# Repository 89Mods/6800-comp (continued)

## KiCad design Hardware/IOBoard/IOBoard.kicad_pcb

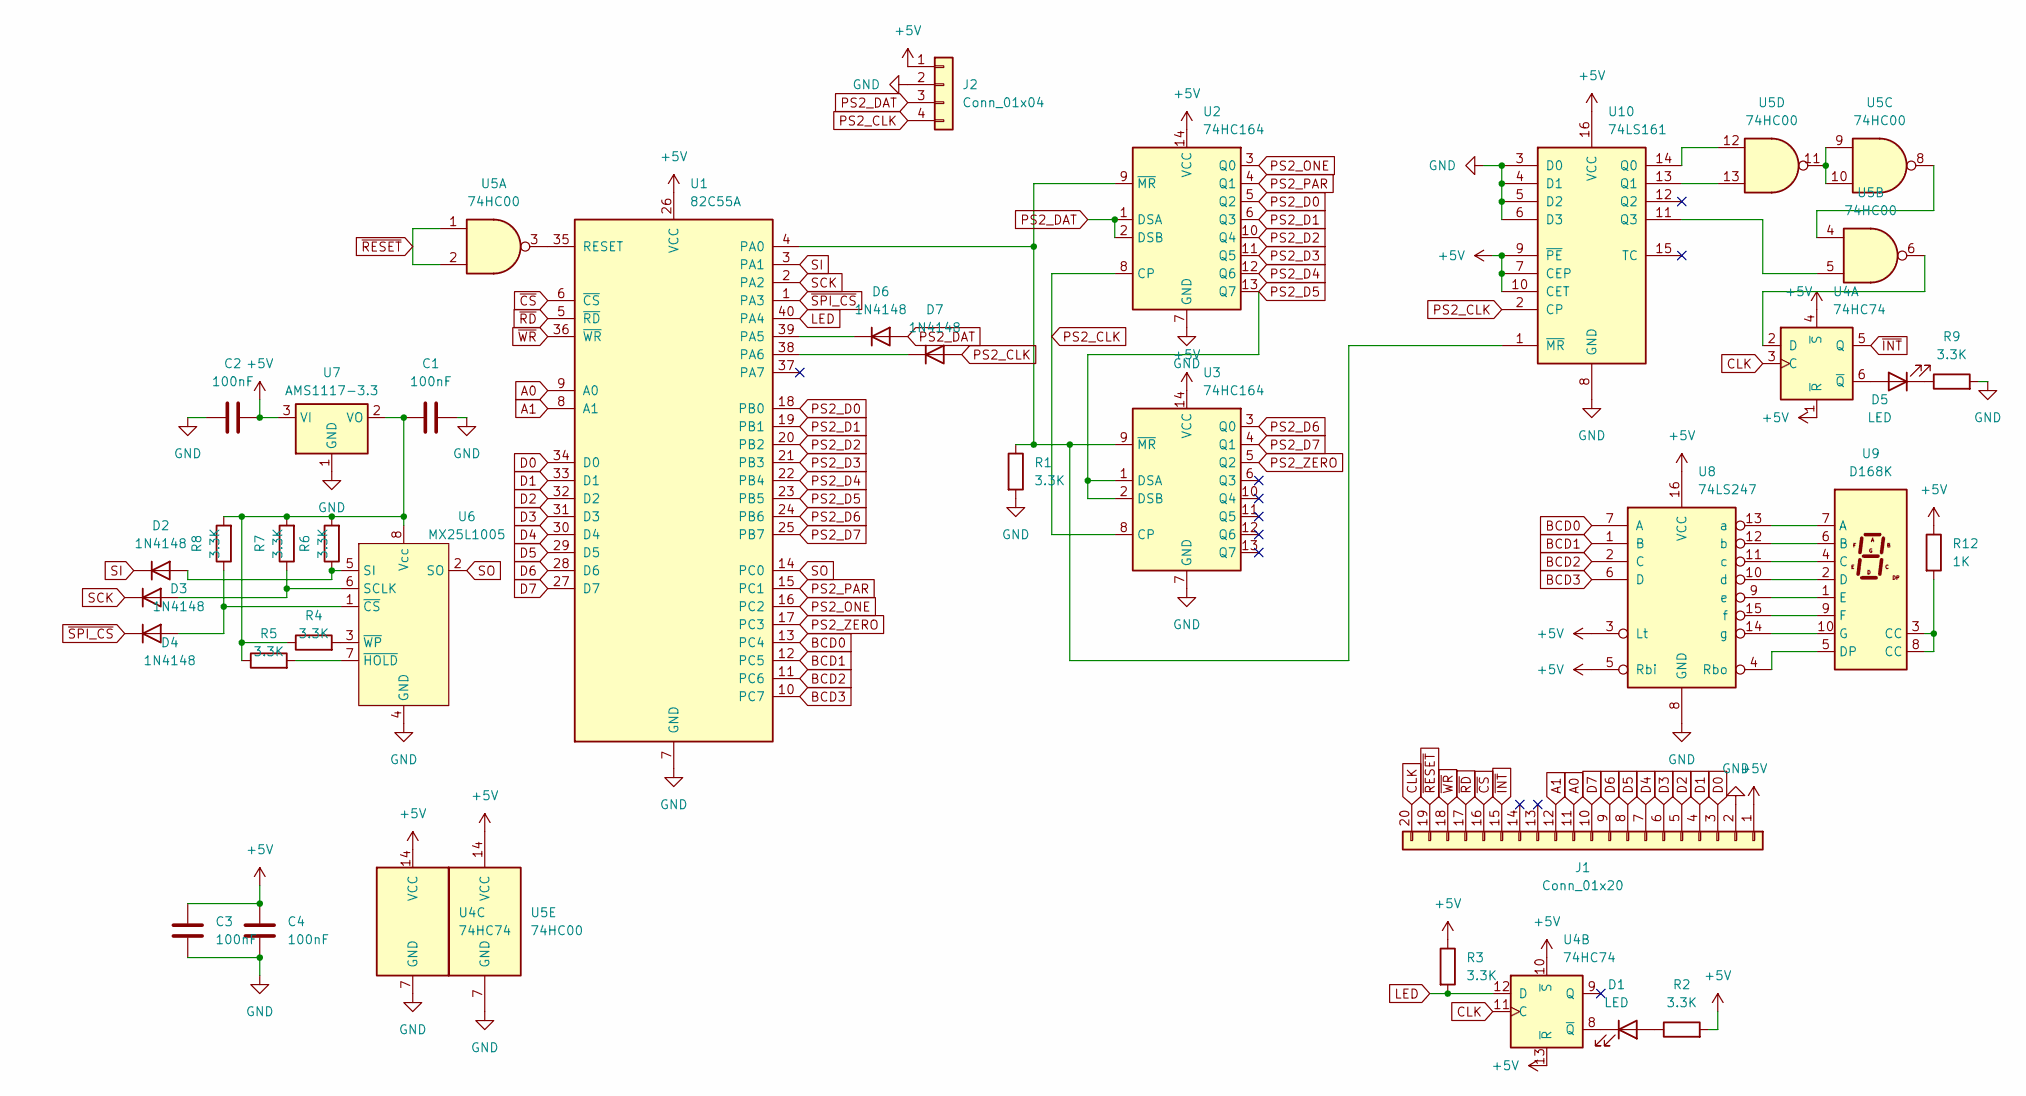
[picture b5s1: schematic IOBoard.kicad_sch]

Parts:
C1, C2, C3, C4: 100nF; C_Disc_D3.0mm_W1.6mm_P2.50mm
D1, D5: LED; LED_D3.0mm
D2, D3, D4, D6, D7: 1N4148; D_DO-34_SOD68_P7.62mm_Horizontal
J1: Conn_01x20; PinHeader_1x20_P2.54mm_Vertical
J2: Conn_01x04; PinHeader_1x04_P2.54mm_Vertical
R1, R2, R3, R4, R5, R6, R7, R8, R9: 3.3K; R_Axial_DIN0204_L3.6mm_D1.6mm_P7.62mm_Horizontal
R12: 1K; R_Axial_DIN0204_L3.6mm_D1.6mm_P7.62mm_Horizontal
U1: 82C55A; DIP-40_W15.24mm
U2, U3: 74HC164; DIP-14_W7.62mm
U4: 74HC74; DIP-14_W7.62mm
U5: 74HC00; DIP-14_W7.62mm
U6: MX25L1005; DIP-8_W7.62mm
U7: AMS1117-3.3; SOT-223-3_TabPin2
U8: 74LS247; DIP-16_W7.62mm
U9: D168K; D1X8K
U10: 74LS161; DIP-16_W7.62mm

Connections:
+5V: C2.2, C3.2, C4.2, J1.1, J2.1, R2.2, R3.1, R12.1, U1.26 (VCC), U2.14 (VCC), U3.14 (VCC), U4.1 (~R), U4.4 (~S), U4.10 (~S), U4.13 (~R), U4.14 (VCC), U5.14 (VCC), U7.3 (VI), U8.3 (Lt), U8.5 (Rbi), U8.16 (VCC), U10.7 (CEP), U10.9 (~PE), U10.10 (CET), U10.16 (VCC)
A0: J1.11, U1.9 (A0)
A1: J1.12, U1.8 (A1)
BCD0: U1.13 (PC4), U8.7 (A)
BCD1: U1.12 (PC5), U8.1 (B)
BCD2: U1.11 (PC6), U8.2 (C)
BCD3: U1.10 (PC7), U8.6 (D)
CLK: J1.20, U4.3 (C), U4.11 (C)
D0: J1.3, U1.34 (D0)
D1: J1.4, U1.33 (D1)
D2: J1.5, U1.32 (D2)
D3: J1.6, U1.31 (D3)
D4: J1.7, U1.30 (D4)
D5: J1.8, U1.29 (D5)
D6: J1.9, U1.28 (D6)
D7: J1.10, U1.27 (D7)
GND: C1.2, C2.1, C3.1, C4.1, J1.2, J2.2, R1.2, R9.2, U1.7 (GND), U2.7 (GND), U3.7 (GND), U4.7 (GND), U5.7 (GND), U6.4 (GND), U7.1 (GND), U8.8 (GND), U10.3 (D0), U10.4 (D1), U10.5 (D2), U10.6 (D3), U10.8 (GND)
LED: R3.2, U1.40 (PA4), U4.12 (D)
unnamed: D1.2 (A), R2.1
unnamed: D1.1 (K), U4.8 (~Q)
unnamed: D2.2 (A), R6.1, U6.5 (SI)
unnamed: D3.2 (A), R7.1, U6.6 (SCLK)
unnamed: D4.2 (A), R8.1, U6.1 (~CS)
unnamed: D5.2 (A), U4.6 (~Q)
unnamed: D5.1 (K), R9.1
unnamed: D6.1 (K), U1.39 (PA5)
unnamed: D7.1 (K), U1.38 (PA6)
unnamed: R12.2, U9.3 (CC), U9.8 (CC)
unnamed: R1.1, U1.4 (PA0), U2.9 (~MR), U3.9 (~MR), U10.1 (~MR)
unnamed: U1.35 (RESET), U5.3
unnamed: U4.2 (D), U5.6
unnamed: U5.4, U5.8
unnamed: U5.9, U5.10, U5.11
unnamed: C1.1, R4.1, R5.1, R6.2, R7.2, R8.2, U6.8 (Vcc), U7.2 (VO)
unnamed: R5.2, U6.7 (~HOLD)
unnamed: R4.2, U6.3 (~WP)
unnamed: U8.4 (Rbo), U9.5 (DP)
unnamed: U8.13 (a), U9.7 (A)
unnamed: U8.12 (b), U9.6 (B)
unnamed: U8.11 (c), U9.4 (C)
unnamed: U8.10 (d), U9.2 (D)
unnamed: U8.9 (e), U9.1 (E)
unnamed: U8.15 (f), U9.9 (F)
unnamed: U8.14 (g), U9.10 (G)
unnamed: U5.12, U10.14 (Q0)
unnamed: U5.13, U10.13 (Q1)
unnamed: U5.5, U10.11 (Q3)
PS2_CLK: D7.2 (A), J2.4, U2.8 (CP), U3.8 (CP), U10.2 (CP)
PS2_D0: U1.18 (PB0), U2.5 (Q2)
PS2_D1: U1.19 (PB1), U2.6 (Q3)
PS2_D2: U1.20 (PB2), U2.10 (Q4)
PS2_D3: U1.21 (PB3), U2.11 (Q5)
PS2_D4: U1.22 (PB4), U2.12 (Q6)
PS2_D5: U1.23 (PB5), U2.13 (Q7), U3.1 (DSA), U3.2 (DSB)
PS2_D6: U1.24 (PB6), U3.3 (Q0)
PS2_D7: U1.25 (PB7), U3.4 (Q1)
PS2_DAT: D6.2 (A), J2.3, U2.1 (DSA), U2.2 (DSB)
PS2_ONE: U1.16 (PC2), U2.3 (Q0)
PS2_PAR: U1.15 (PC1), U2.4 (Q1)
PS2_ZERO: U1.17 (PC3), U3.5 (Q2)
SCK: D3.1 (K), U1.2 (PA2)
SI: D2.1 (K), U1.3 (PA1)
SO: U1.14 (PC0), U6.2 (SO)
~CS: J1.16, U1.6 (~CS)
~INT: J1.15, U4.5 (Q)
~RD: J1.17, U1.5 (~RD)
~RESET: J1.19, U5.1, U5.2
~SPI_CS: D4.1 (K), U1.1 (PA3)
~WR: J1.18, U1.36 (~WR)

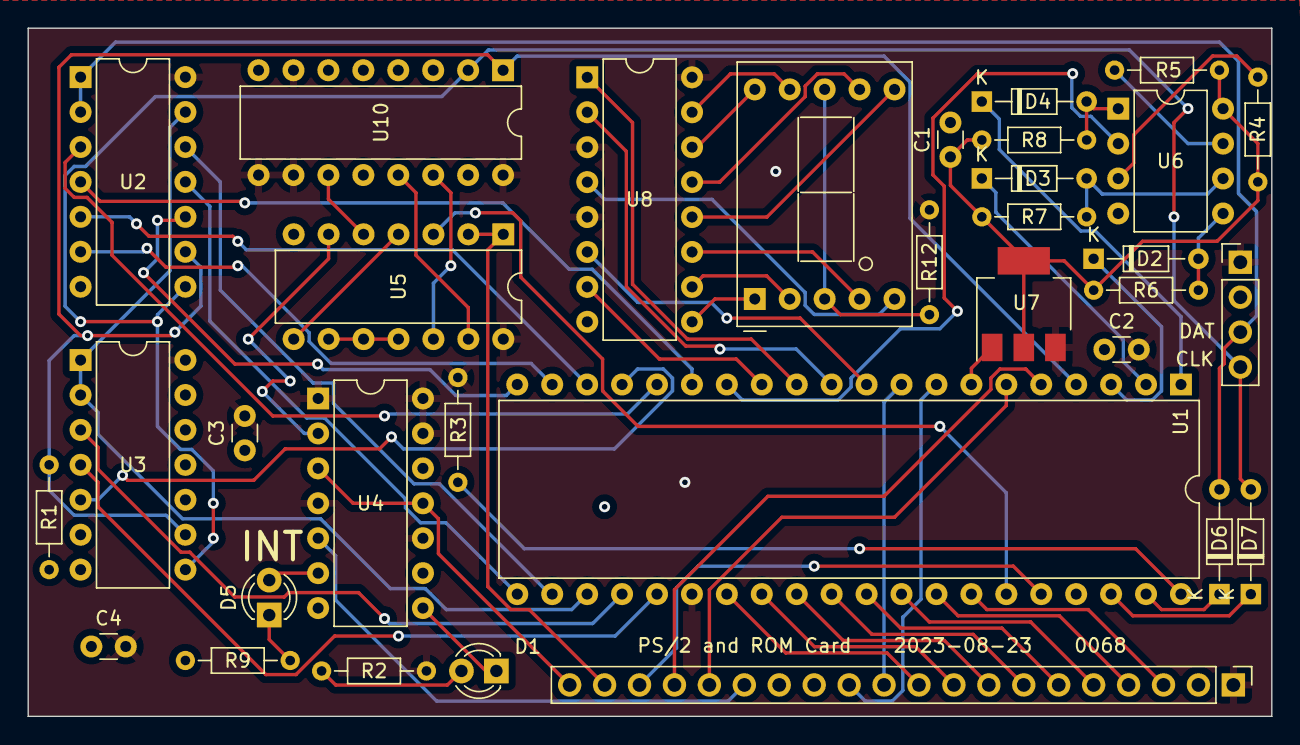
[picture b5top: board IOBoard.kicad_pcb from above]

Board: 4 copper layers, 90.4 x 50.0 mm, 33 parts (0 on the bottom side), 69 nets.

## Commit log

2024-07-02 Initial commit.
2024-07-02 Fix menu software using incorrect flash base address on 6809.
